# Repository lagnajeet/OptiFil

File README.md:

# OptiFil
Optical Filament Sensor

This filament sensor is based on the same principle that makes optical mouse work. The sennsor used in here is an ADNS9800 and the processor is an ESP8285. The filament moves infront of the optical mouse sensor and the surface property and speed of the sensor is used to determine runouts and jams.
<p align="center">

  <i>Green - Normal Operation, Red - Filament Runout, Purple - Filament Jammed</i>
</p>
The various settings of the sensor can be set from the web interface. The device exposes itself as a SSDP service.Below is a acreenshot of the web interface.

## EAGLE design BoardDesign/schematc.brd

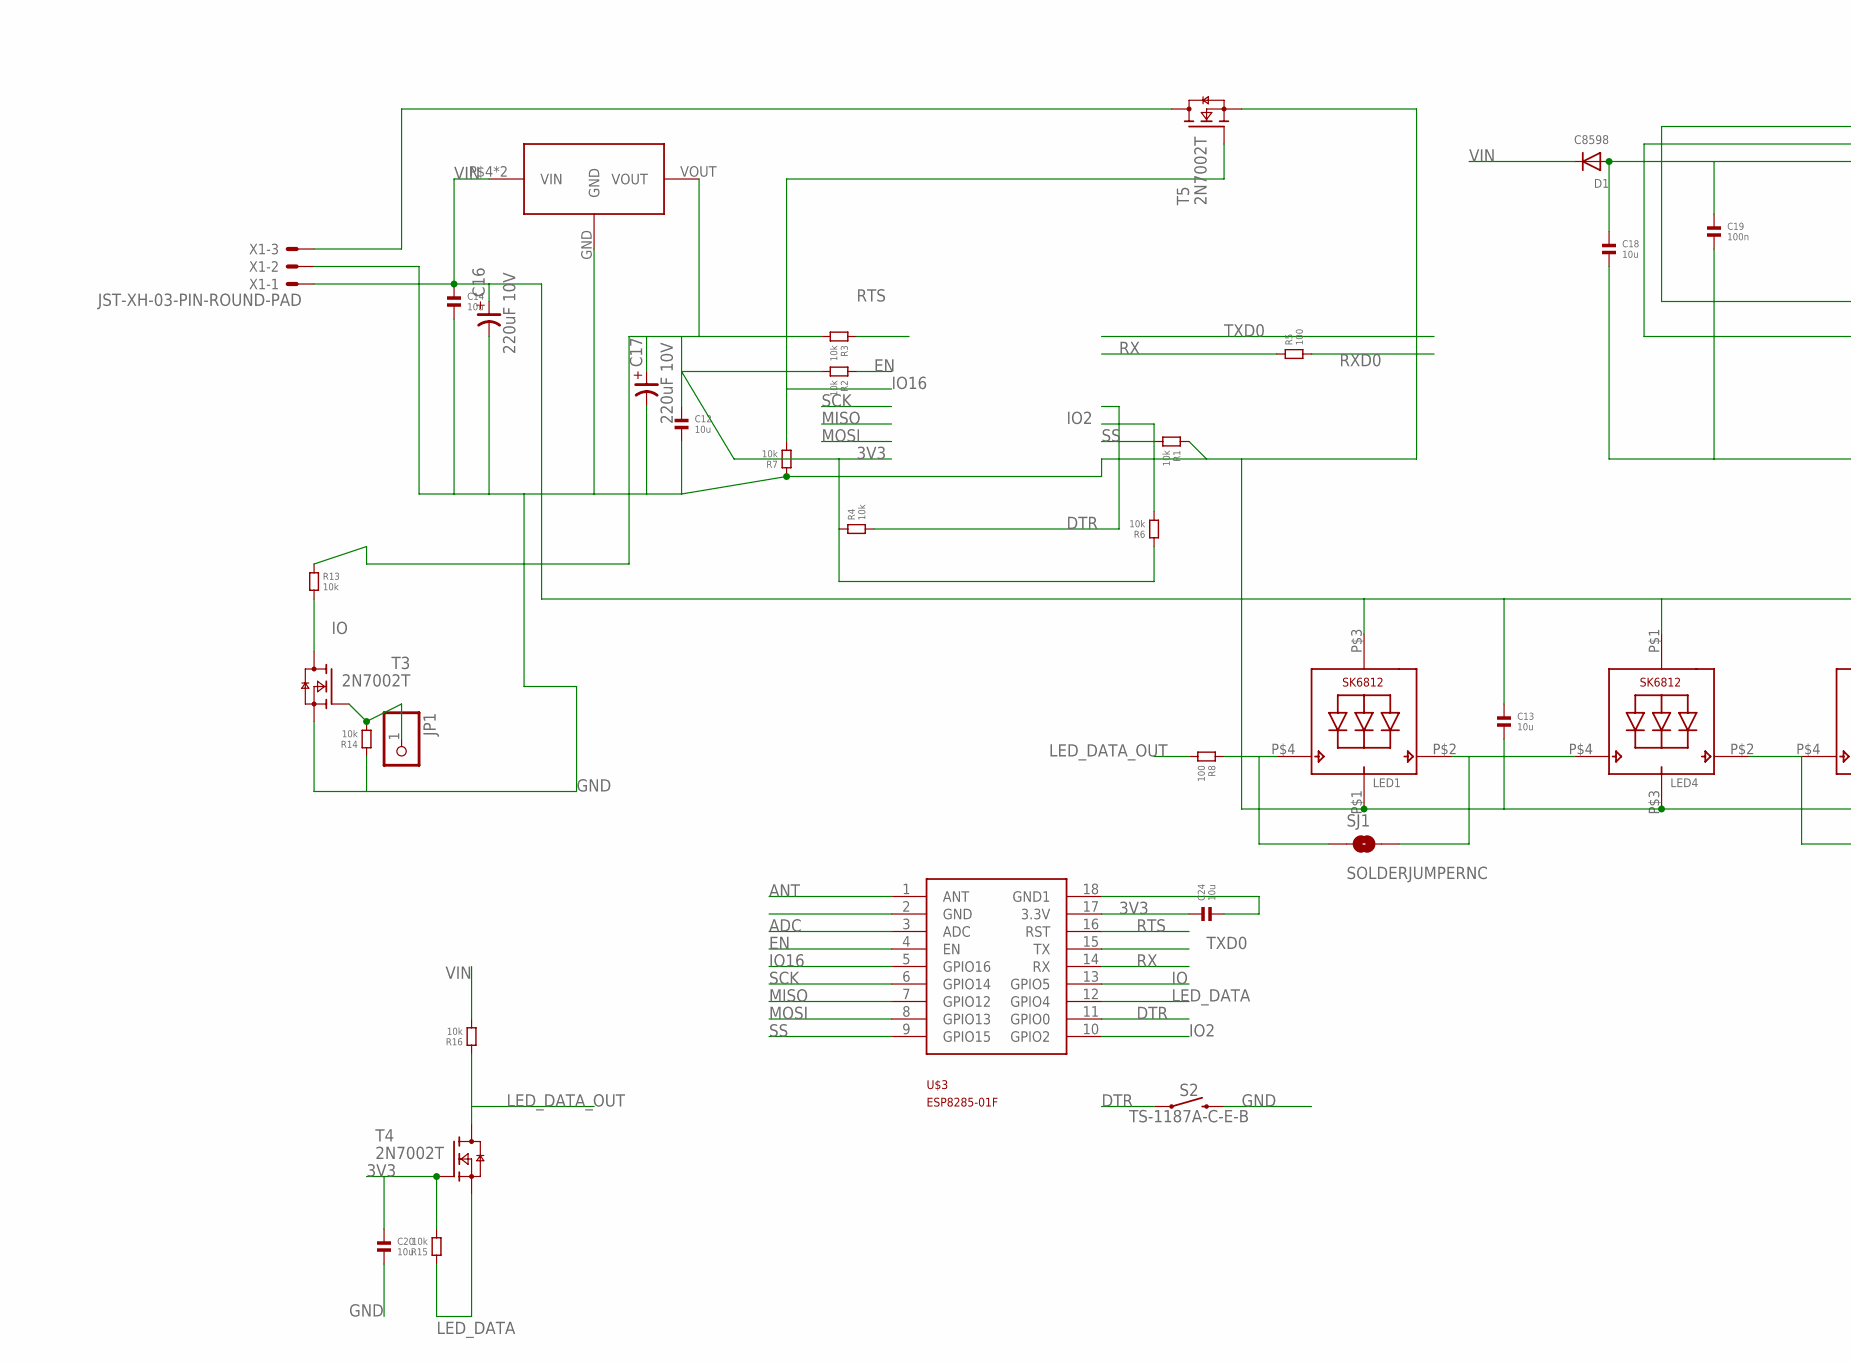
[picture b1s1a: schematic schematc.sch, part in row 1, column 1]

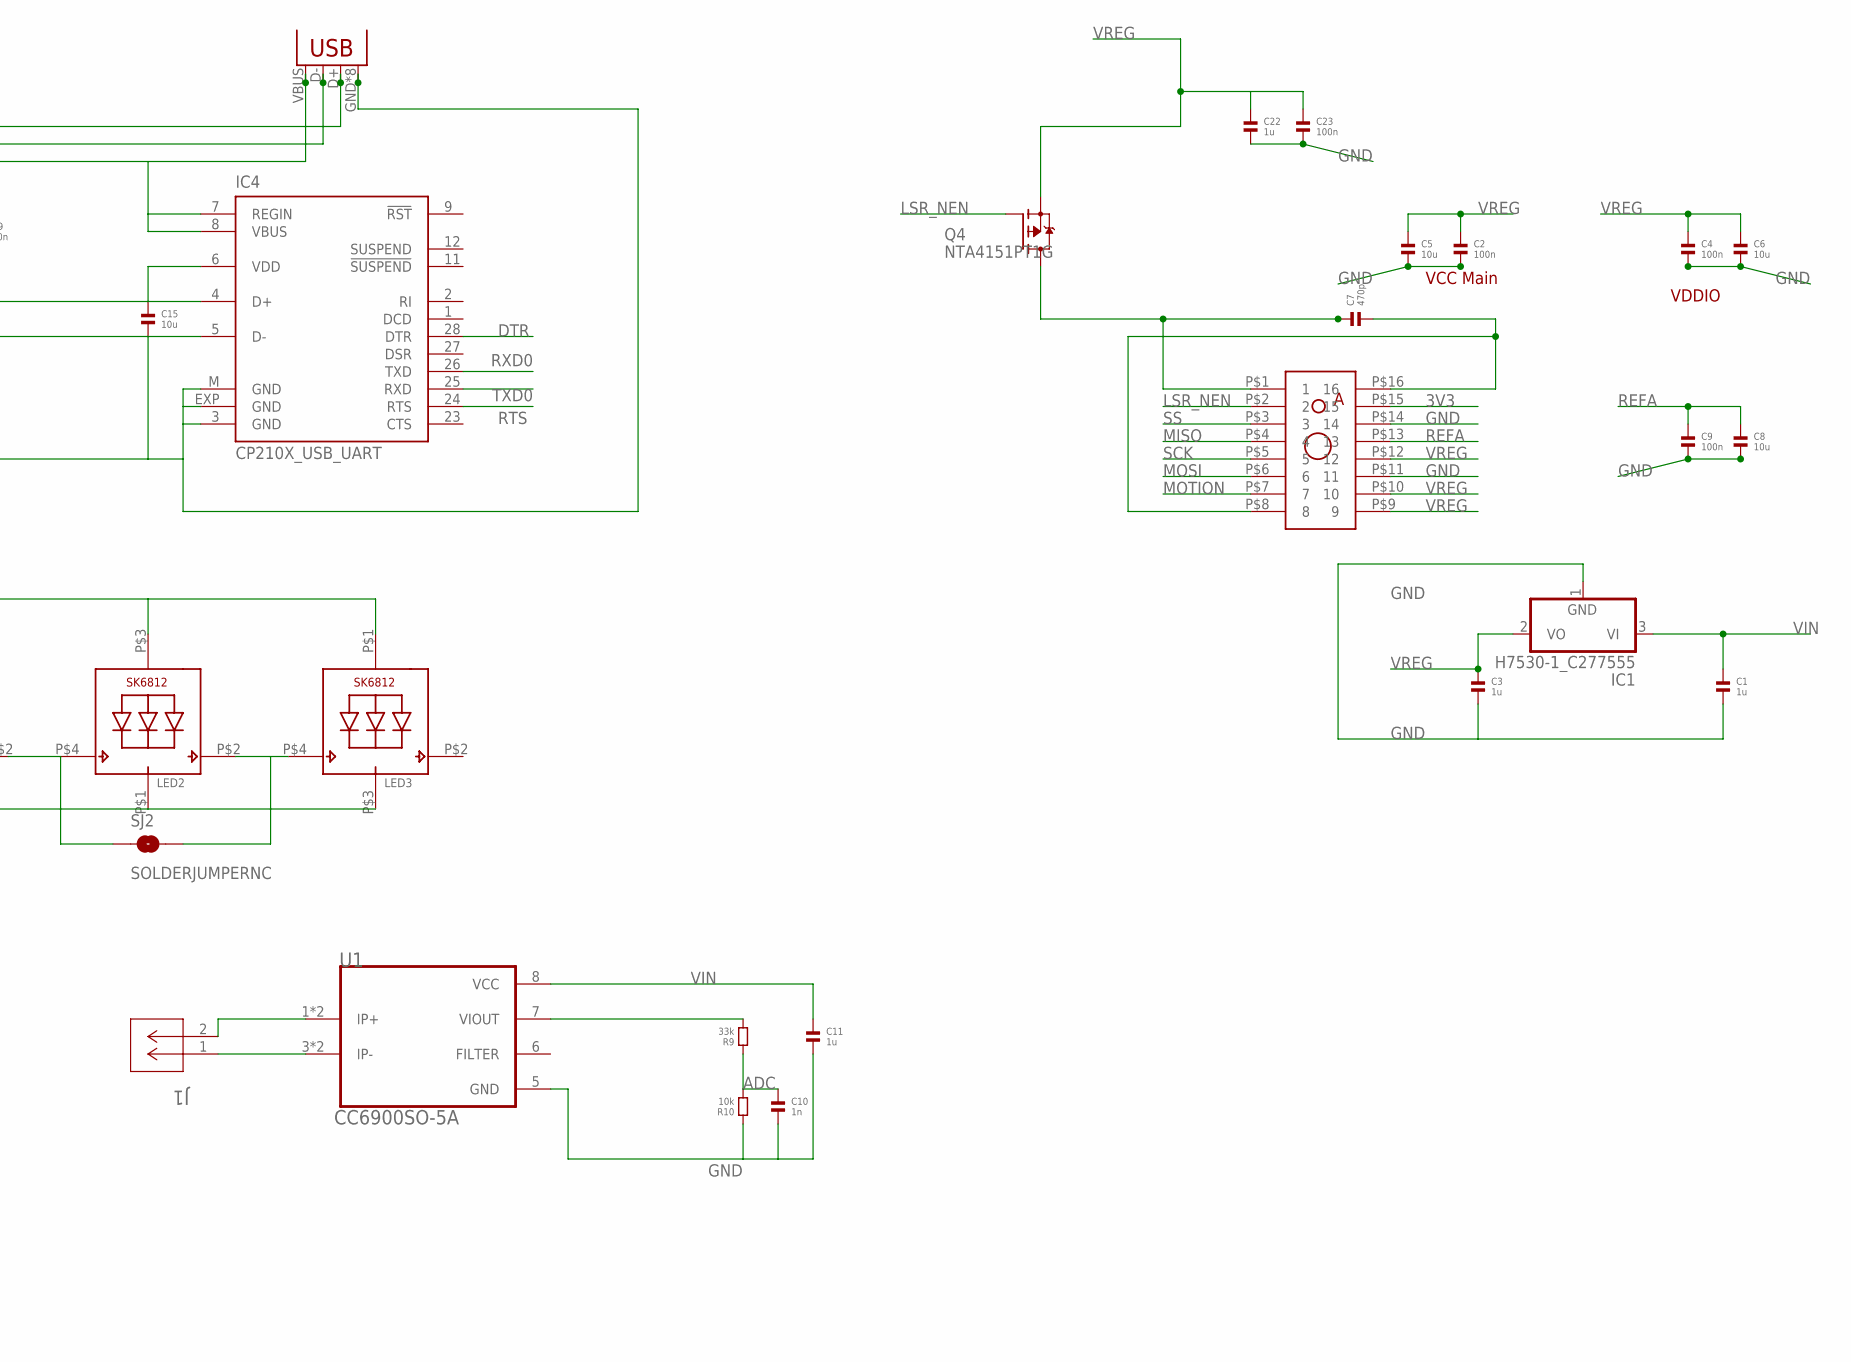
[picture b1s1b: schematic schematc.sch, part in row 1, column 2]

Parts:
C1, C3, C11, C22: 1u; 0402
C2, C4, C9, C19, C23: 100n; 0402
C5, C6, C8, C12, C13, C14, C15, C18, C20, C24: 10u; 0402
C7: 470p; 0402
C10: 1n; 0402
C16, C17: 220uF 10V; 3528-TE-B
D1: C8598; SOD-123
IC1: H7530-1_C277555; SOT23
IC4: CP210X_USB_UART; MLP28
J1: JST; CONN_S2B-PH-K-S_JST
JP1: PINHD-1X1CB; 1X01-CLEANBIG
LED1, LED2: SK6812_SIDE; LEDSIDE
LED3, LED4: SK6812_2020; _2020
Q4: NTA4151PT1G; SC75_INFINEON
R1, R2, R3, R4, R6, R7, R10, R13, R14, R15, R16: 10k; 0402
R5, R8: 100; 0402
R9: 33k; 0402
S2: TS-1187A-C-E-B; TACTILE_SWITCH_SMD_5.2MM
SJ1, SJ2: SOLDERJUMPERNC; SJ_2S_SMALL
T3, T4, T5: 2N7002T; SOT416
U1: CC6900SO-5A; SOIC127P600X175-8N
U$1: AVAGO_ADNS-9500
U$3: ESP8285_ESP-01F01F; ESP8285-01F
U$5: ME6119; SOT89
USB1: USBMICROB-PTH; USB-MICROB-TH
X1: JST-XH-03-PIN-ROUND-PAD; JST-XH-03-PACKAGE-ROUND-PAD

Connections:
3V3: C12.1, C17.+, C20.1, C24.1, R2.2, R3.2, R4.1, R6.1, R13.1, R15.2, T4.1 (G), U$1.P$15 (15), U$3.17 (3.3V), U$5.VOUT
ADC: C10.1, R9.1, R10.2, U$3.3 (ADC)
ANT: U$3.1 (ANT)
DTR: IC4.28 (DTR), R4.2, S2.1, S2.2 (1), U$3.11 (GPIO0)
EN: R2.1, U$3.4 (EN)
GND: C1.2, C2.2, C3.2, C4.2, C5.2, C6.2, C8.2, C9.2, C10.2, C11.2, C12.2, C13.2, C14.2, C15.2, C16.-, C17.-, C18.2, C19.2, C20.2, C22.2, C23.2, C24.2, IC1.1 (GND), IC4.3 (GND), IC4.EXP (GND), IC4.M (GND), LED1.P$1 (GND), LED2.P$1 (GND), LED3.P$3 (GND), LED4.P$3 (GND), R1.1, R7.1, R10.1, R14.1, S2.3 (2), S2.4 (2), T3.2 (S), T5.2 (S), U1.5 (GND), U$1.P$11 (11), U$1.P$14 (14), U$3.2 (GND), U$3.18 (GND1), U$5.GND, USB1.GND, USB1.ID (GND), USB1.M5 (GND), USB1.M6 (GND), USB1.MT1 (GND), USB1.MT2 (GND), USB1.MT3 (GND), USB1.MT4 (GND), X1.2
IO: R13.2, T3.3 (D), U$3.13 (GPIO5)
IO2: R6.2, U$3.10 (GPIO2)
IO16: R7.2, T5.1 (G), U$3.5 (GPIO16)
LED_DATA: R15.1, T4.2 (S), U$3.12 (GPIO4)
LED_DATA_OUT: R8.2, R16.1, T4.3 (D)
LSR_NEN: Q4.1 (G), U$1.P$2 (2)
MISO: U$1.P$4 (4), U$3.7 (GPIO12)
MOSI: U$1.P$6 (6), U$3.8 (GPIO13)
MOTION: U$1.P$7 (7)
unnamed: C7.2, U$1.P$8 (8), U$1.P$16 (16)
unnamed: C7.1, Q4.2 (D), U$1.P$1 (1)
unnamed: J1.2, U1.1 (IP+), U1.2 (IP+)
unnamed: J1.1, U1.3 (IP-), U1.4 (IP-)
unnamed: R9.2, U1.7 (VIOUT)
unnamed: LED1.P$2 (DO), LED4.P$4 (DI), SJ1.2
unnamed: LED1.P$4 (DI), R8.1, SJ1.1
unnamed: LED2.P$2 (DO), LED3.P$4 (DI), SJ2.2
unnamed: LED2.P$4 (DI), LED4.P$2 (DO), SJ2.1
unnamed: JP1.1, R14.2, T3.1 (G)
unnamed: T5.3 (D), X1.3
unnamed: C18.1, C19.1, D1.A, IC4.7 (REGIN), IC4.8 (VBUS), USB1.VBUS
unnamed: C15.1, IC4.6 (VDD)
unnamed: IC4.5 (D-), USB1.D-
unnamed: IC4.4 (D+), USB1.D+
REFA: C8.1, C9.1, U$1.P$13 (13)
RTS: IC4.24 (RTS), R3.1, U$3.16 (RST)
RX: R5.1, U$3.14 (RX)
RXD0: IC4.26 (TXD), R5.2
SCK: U$1.P$5 (5), U$3.6 (GPIO14)
SS: R1.2, U$1.P$3 (3), U$3.9 (GPIO15)
TXD0: IC4.25 (RXD), U$3.15 (TX)
VIN: C1.1, C11.1, C13.1, C14.1, C16.+, D1.C, IC1.3 (VI), LED1.P$3 (VDD), LED2.P$3 (VDD), LED3.P$1 (VDD), LED4.P$1 (VDD), R16.2, U1.8 (VCC), U$5.P$4 (VIN), U$5.VIN, X1.1
VREG: C2.1, C3.1, C4.1, C5.1, C6.1, C22.1, C23.1, IC1.2 (VO), Q4.3 (S), U$1.P$9 (9), U$1.P$10 (10), U$1.P$12 (12)

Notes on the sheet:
VDDIO
VCC Main

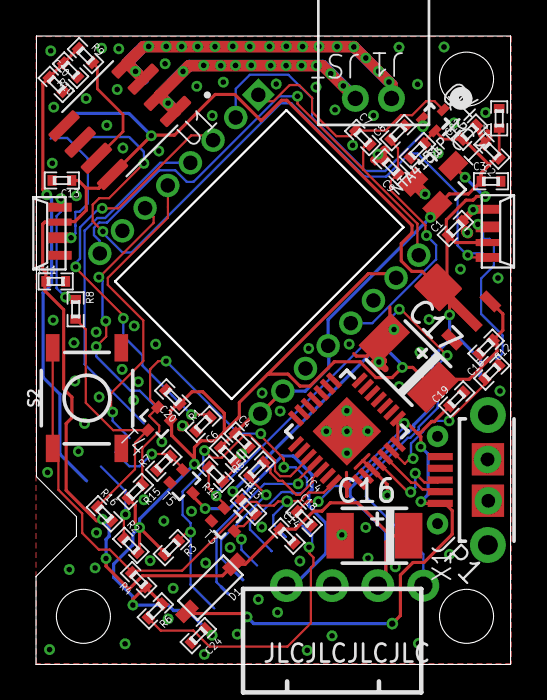
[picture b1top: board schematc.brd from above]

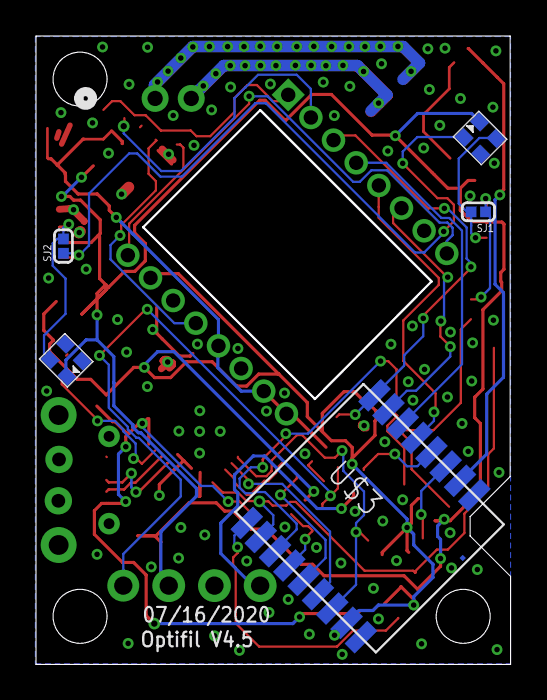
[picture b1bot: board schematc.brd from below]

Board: 2 copper layers, 26.2 x 34.8 mm, 59 parts (5 on the bottom side), 37 nets.

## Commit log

2021-02-23 schematic and layout files
    Eagle schematic and layout file along with the gerber file, BOM and PicknPlace file for manufacturing.
2021-02-23 Firmware for Optical filament sensor
    Esp8285 firmware that run the OptiFil Sensor.
2021-03-01 Top and bottom 3D print STL Files
2021-03-01 SVG files for Lasercut

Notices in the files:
parts and their libraries:
SparkFun-DigitalIC: Licensing: CC v3.0 Share-Alike You are welcome to use this library for commercial purposes.
SparkFun-Switches: Licensing: Creative Commons ShareAlike 4.0 International - https://creativecommons.org/licenses/by-sa/4.0
